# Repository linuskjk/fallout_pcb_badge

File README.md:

# Fallout PCB Badge

A unique Fallout-inspired PCB name badge that doesn't look boring like most convention badges.

This badge combines hardware and software into a functional wearable featuring animated LEDs, NFC support, and multiple lighting modes.

## Features

- Multiple LED animation modes
- Push button to cycle through effects
- Integrated NFC functionality
- Custom-designed NFC antenna coil
- Powered by a microcontroller
- Stylish PCB badge design inspired by the Fallout universe

## NFC

The badge includes a custom NFC coil connected to an NFC controller.

Program it with your own data, such as:
- Your website
- GitHub profile
- LinkedIn
- Portfolio
- Contact information
- Any URL of your choice

Anyone can simply tap the badge with their NFC-enabled phone to instantly access your link.

## Preview

## Future Ideas

- Battery-powered version
- USB-C programming
- More LED animations
- Interactive NFC features
- Sound effects

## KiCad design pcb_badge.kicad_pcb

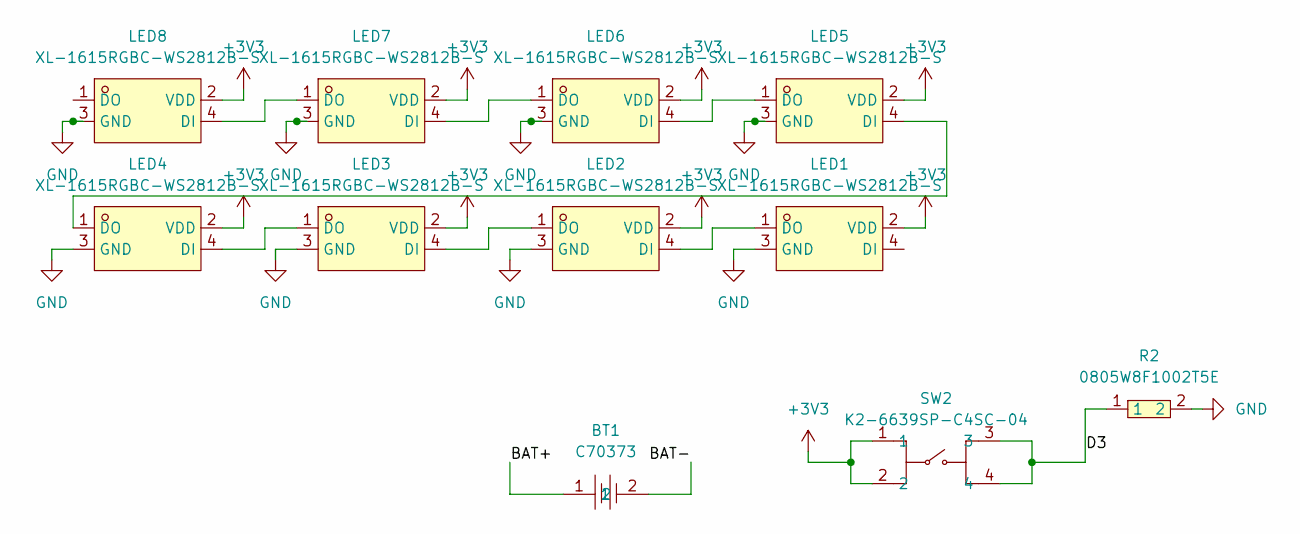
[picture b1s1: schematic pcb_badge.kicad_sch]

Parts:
BT1: C70373; BAT-SMD_CR2032_C70373; LCSC Part C70373
LED1, LED2, LED3, LED4, LED5, LED6, LED7, LED8: XL-1615RGBC-WS2812B-S; LED-SMD_4P-L1.6-W1.5_XL-1615RGBC-WS2812B-S; LCSC Part C41413180
R2: 0805W8F1002T5E; R0805; LCSC Part C17414
SW2: K2-6639SP-C4SC-04; KEY-SMD_4P-L6.0-W6.0-P3.90-LS9.0; LCSC Part C83206

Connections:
+3V3: LED1.2 (VDD), LED2.2 (VDD), LED3.2 (VDD), LED4.2 (VDD), LED5.2 (VDD), LED6.2 (VDD), LED7.2 (VDD), LED8.2 (VDD), SW2.1, SW2.2
/D3: R2.1, SW2.3, SW2.4
GND: LED1.3 (GND), LED2.3 (GND), LED3.3 (GND), LED4.3 (GND), LED5.3 (GND), LED6.3 (GND), LED7.3 (GND), LED8.3 (GND), R2.2
unnamed: LED1.1 (DO), LED2.4 (DI)
unnamed: LED2.1 (DO), LED3.4 (DI)
unnamed: LED3.1 (DO), LED4.4 (DI)
unnamed: LED4.1 (DO), LED5.4 (DI)
unnamed: LED5.1 (DO), LED6.4 (DI)
unnamed: LED6.1 (DO), LED7.4 (DI)
unnamed: LED7.1 (DO), LED8.4 (DI)

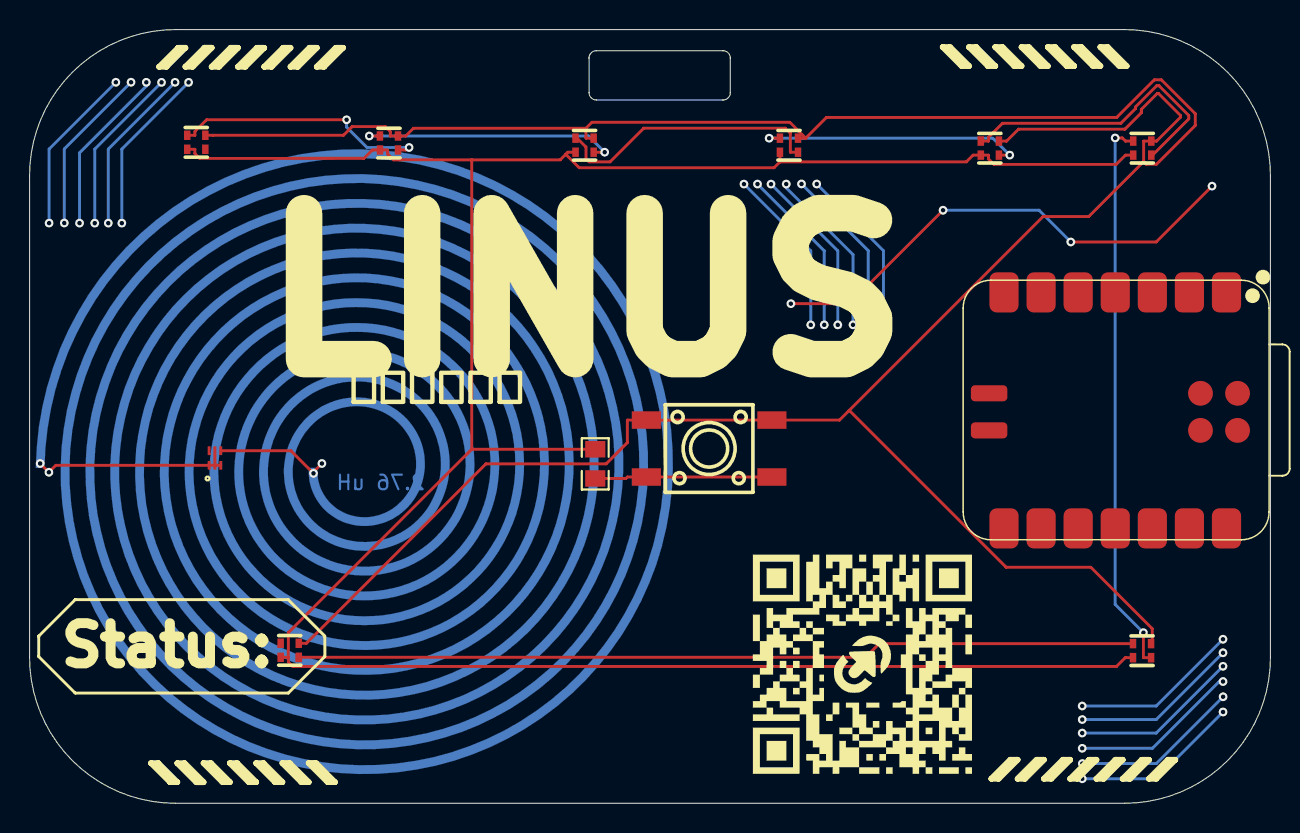
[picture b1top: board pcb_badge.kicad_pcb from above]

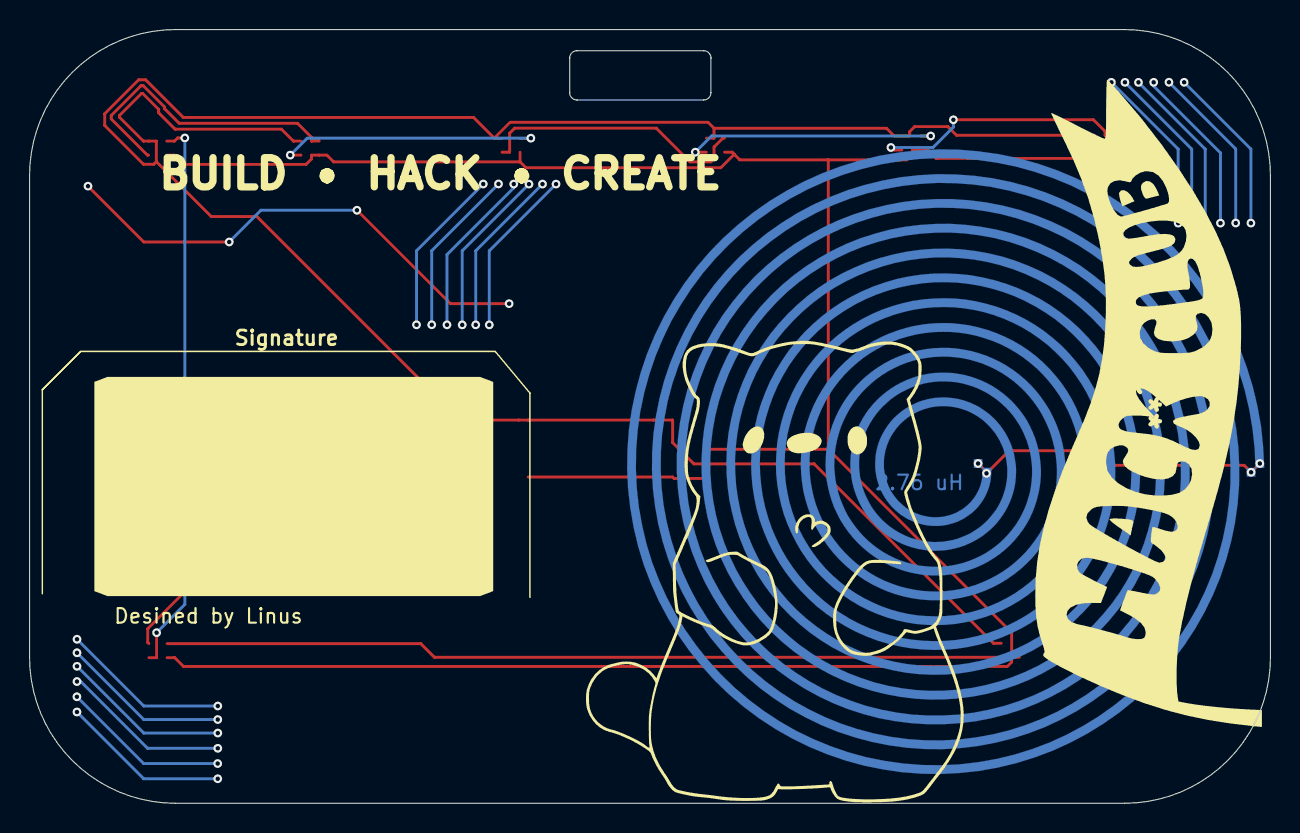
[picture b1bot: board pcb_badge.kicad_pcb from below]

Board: 2 copper layers, 85.0 x 53.0 mm, 15 parts (3 on the bottom side), 10 nets.

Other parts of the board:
C**: LOGO
L**: 2.76 uH; NFC_COIL
P***: LOGO
REEF**: Val**; XIAO-RP2040-SMD
Y***: LOGO
